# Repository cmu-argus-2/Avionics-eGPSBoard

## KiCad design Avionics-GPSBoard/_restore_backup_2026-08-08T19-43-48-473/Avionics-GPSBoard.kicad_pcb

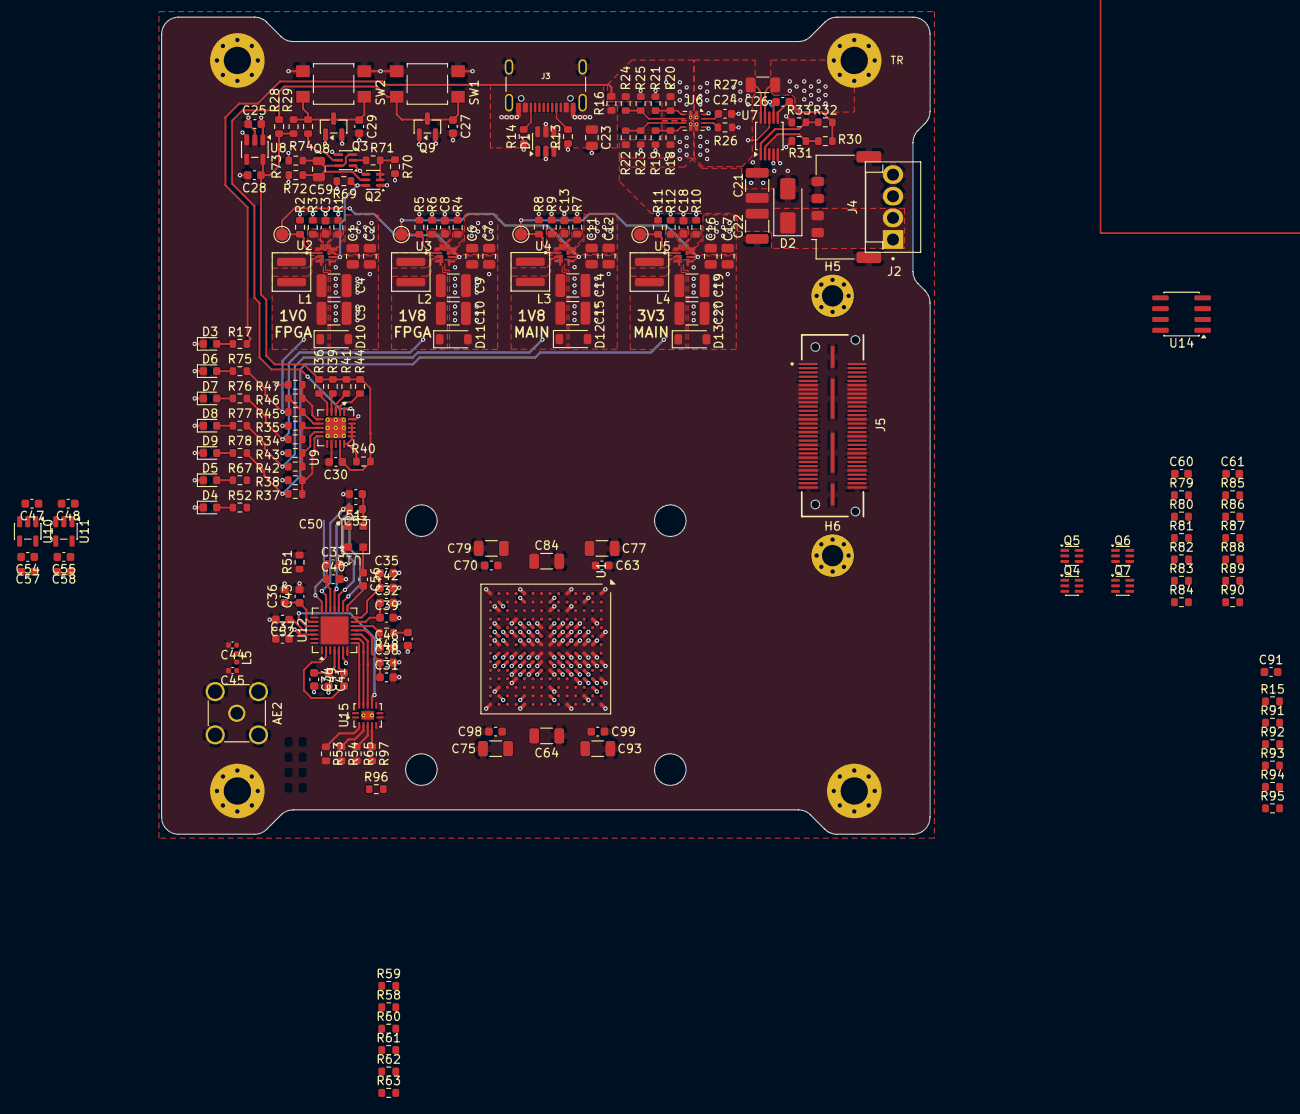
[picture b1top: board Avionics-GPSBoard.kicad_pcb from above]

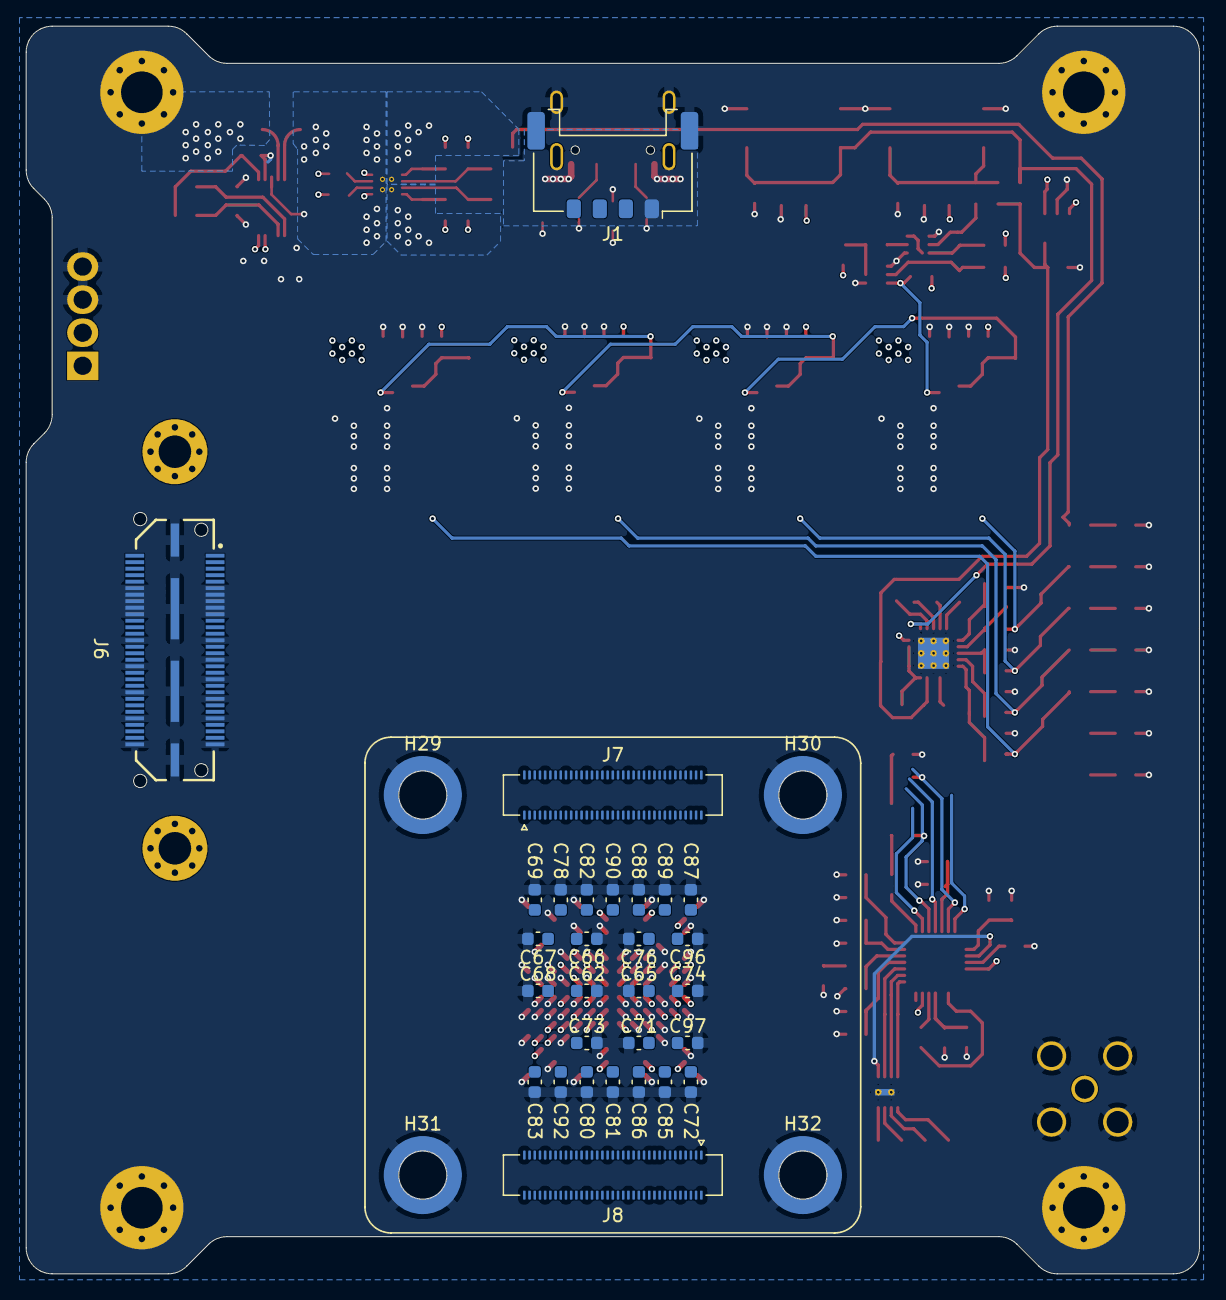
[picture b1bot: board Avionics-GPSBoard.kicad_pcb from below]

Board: 4 copper layers, 90.2 x 95.9 mm, 252 parts (33 on the bottom side), 119 nets.

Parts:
AE2: Antenna_Shield; SMA_Amphenol_132134-11_Vertical
C1, C2, C6, C7, C11, C12, C16, C17, C59: 10u; C_0805_2012Metric
C3, C8, C13, C18: 3n3; C_0603_1608Metric
C4, C5, C9, C10, C14, C15, C19, C20, C21, C22: 22u; C_1210_3225Metric
C23: 4u7; C_0805_2012Metric
C24: TBD; C_0603_1608Metric
C25, C47, C48, C54, C55: 1u; C_0603_1608Metric
C26, C27, C29, C30, C31, C32, C33, C34, C35, C36, C51, C57, C58: 100n; C_0603_1608Metric
C28: 2.2u; C_0603_1608Metric
C37, C49, C50: 470p; C_0603_1608Metric
C38, C39, C40, C41, C42, C43, C52: 100p; C_0603_1608Metric
C44, C45: TBD; C_0402_1005Metric
C46: 27p; C_0603_1608Metric
C53, C56, C60, C61: 10n; C_0603_1608Metric
C62, C65, C66, C67, C68, C71, C73, C74, C76, C80, C81, C82, C85, C86, C88, C89, C90, C96, C97: 470n; C_0603_1608Metric
C63, C69, C70, C72, C78, C83, C87, C91, C92, C98, C99: 4.7u; C_0603_1608Metric
C64, C79: 100u; C_1206_3216Metric
C75, C77, C84, C93: 47u; C_1206_3216Metric
D1: USBLC6-2SC6; SOT-23-6
D2: SMAJ9.0AHR3G; D_SMA
D3: Green; LED_0603_1608Metric
D4, D5: LED_G_0603_LTST-C190KRKT; LED_0603_1608Metric
D6, D7, D8, D9: LED_G_0603_LTST-C190GKT; LED_0603_1608Metric
D10, D11, D12, D13: SZMMSZ4685T1G; D_SOD-123
H1, H2, H3, H4: MountingHole_Pad; MountingHole_3.2mm_M3_Pad_Via
H5, H6: MountingHole_Pad; MountingHole_2.5mm_Pad_Via
H29, H30, H31, H32: 9774030151R; Mounting_Wuerth_WA-SMSI-M2.5_H3mm_9774030151
J1, J2: 205338-0004; Molex_Pico-Lock_205338-0004_1x04-1MP_P2.00mm_Horizontal
J3: USB4105-GF-A; USB_C_Receptacle_GCT_USB4105-xx-A_16P_TopMnt_Horizontal
J4: 282834-4; TE_282834-4
J5: QSH-030-01-L-D-A; SAMTEC_QSH-030-01-L-D-A
J6: QTH-030-01-L-D-A; SAMTEC-QTH-030-01-X-D-A
J7, J8: DF40HC(3.0)-70DS-0.4V; Hirose_DF40C-70DS-0.4V_2x35_P0.4mm
L1, L2, L3, L4: 2.2uH; L_Coilcraft_XAL4020-XXX
L5: 0R; L_0402_1005Metric
Q2, Q3, Q5, Q7: MBT2222ADW1T1; SOT-363_SC-70-6
Q4, Q6: NX3008NBKS; SOT-363_SC-70-6
Q8, Q9: BSS138; SOT-23
R1, R4, R7, R10: 61.9k; R_0603_1608Metric
R2, R5, R8, R11: 22k; R_0603_1608Metric
R3: 8.87k; R_0603_1608Metric
R6, R9: 21k; R_0603_1608Metric
R12: OPEN; R_0603_1608Metric
R13, R14: 5k1; R_0603_1608Metric
R15, R91, R92, R93, R94, R95: 1K; R_0603_1608Metric
R16, R30, R31, R32, R33, R51, R53, R54, R65, R81, R87, R97: 0R; R_0603_1608Metric
R17: 4k7; R_0603_1608Metric
R18, R19, R20, R21, R22, R23, R24, R25, R26, R34, R35, R37, R38, R40, R42, R43, R45, R46, R47: TBD; R_0603_1608Metric
R27: 10m; R_1206_3216Metric
R28, R29, R74, R82, R83, R88, R89, R96: 10k; R_0603_1608Metric
R36, R39, R41, R44, R70, R73, R80, R86: 100k; R_0603_1608Metric
R48, R71: 20k; R_0603_1608Metric
R52, R67, R75, R76, R77, R78: 2k7; R_0603_1608Metric
R58, R59, R60, R61, R62, R63: 33; R_0603_1608Metric
R69: 73k2; R_0603_1608Metric
R72, R84, R90: 200k; R_0603_1608Metric
R79, R85: 680R; R_0603_1608Metric
SW1, SW2: SW_Push; SW_SPST_TL3305A
TP1, TP2, TP3, TP4: TestPoint; TestPoint_Pad_D1.5mm
U1: XC7S50-L1FTGB196I; Xilinx_FTGB196
U2, U3, U4, U5: TPS62902QRYTRQ1
U6: TPS2121RUXR; Texas_VQFN-HR-12_2x2.5mm_P0.5mm_ThermalVias
U7: INA226-Q1; TSSOP-10_3x3mm_P0.5mm
U8: TPS70933DBVR-Q1; SOT-23-5
U9: TPS386000RGPR-Q1; Texas_RGP0020H_VQFN-20-1EP_4x4mm_P0.5mm_EP2.4x2.4mm_Thermal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
U10, U11: TPS7A20285PDBVR; SOT-23-5
U12: MAX2769BETI_V_T; TQFN-28-1EP_5x5mm_P0.5mm_EP3.25x3.25mm
U13: D32G-016_368M
U14: APS1604M-3SQRx-SN; SOIC-8_3.9x4.9mm_P1.27mm
U15: NXU0104BQ; DHVQFN-14-1EP_2.5x3mm_P0.5mm_EP1x1.5mm_ThermalVias

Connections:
2V85_RF_A: C31.1, C32.1, C34.1, C35.1, C36.1, C38.1, C39.1, C41.1, C42.1, C43.1, C54.1, C57.1, R52.1, U10.5 (OUT), U12.4 (VCCRF), U12.11 (VCCVCO), U12.13 (VCCCP), U12.14 (VCCD), U12.23 (VCCIF)
2V85_RF_D: C33.1, C40.1, C51.1, C53.1, C55.1, C58.1, R67.1, R96.1, U11.5 (OUT), U12.19 (VCCADC), U13.4 (VCC), U15.8 (OE), U15.14 (VCCB)
+1V0_F: C4.2, C5.2, C62.1, C63.1, C64.1, C65.1, C66.1, C67.1, C68.1, C69.1, C70.1, C76.1, C77.1, C78.1, C79.1, D10.1 (K), L1.2, R45.2, R75.2, U1.D6 (VCCINT), U1.D8 (VCCINT), U1.E5 (VCCBRAM), U1.E7 (VCCINT), U1.E9 (VCCINT), U1.F6 (VCCINT), U1.G5 (VCCBRAM), U1.G9 (VCCINT), U1.H6 (VCCINT), U1.J5 (VCCBRAM), U1.J9 (VCCINT), U1.K6 (VCCINT), U1.K8 (VCCINT), U2.3 (VOS)
+1V8_DCDC: J8.3, J8.5, J8.7
+1V8_F: C9.2, C10.2, C71.1, C72.1, C73.1, C74.1, C75.1, C80.1, C81.1, C82.1, C83.1, C84.1, C85.1, C86.1, C87.1, C88.1, C89.1, C90.1, C91.1, C92.1, C93.1, C96.1, C97.1, C98.1, C99.1, D11.1 (K), L2.2, R15.1, R34.2, R76.2, R92.1, R94.1, U1.F8 (VCCADC_0), U1.F10 (VCCAUX), U1.G2 (VCCO_34), U1.G13 (VCCO_14), U1.H10 (VCCAUX), U1.K2 (VCCO_34), U1.K10 (VCCAUX), U1.K13 (VCCO_14), U1.L9 (VCCAUX), U1.N2 (VCCO_34), U1.N6 (VCCO_0), U1.N8 (VCCO_0), U1.N13 (VCCO_14), U3.3 (VOS), U14.8 (VDD)
+1V8_M: C14.2, C15.2, D12.1 (K), L3.2, R42.2, R77.2, U4.3 (VOS), U15.1 (VCCA)
+3V3_M: C19.2, C20.2, C26.2, C47.1, C48.1, D13.1 (K), L4.2, R30.2, R32.2, R37.2, R78.2, R80.1, R82.1, R83.1, R86.1, R88.1, R89.1, U5.3 (VOS), U7.6 (VS), U10.1 (IN), U11.1 (IN)
+3V3_SUP: C28.1, C30.2, R28.1, R29.1, R36.1, R39.1, R40.1, R41.1, R44.1, U8.5 (OUT), U9.14 (VCC)
/FPGA/MODE0: R15.2, R91.1, U1.M7 (M0_0)
/FPGA/MODE1: R92.2, R93.1, U1.M8 (M1_0)
/FPGA/MODE2: R94.2, R95.1, U1.M9 (M2_0)
/FPGA/QSPI_CS: U1.C11 (IO_L6P_T0_FCS_B_14), U14.1 (~CE)
/FPGA/QSPI_DO0: U1.B11 (IO_L1P_T0_D00_MOSI_14), U14.5 (SI/SIO0)
/FPGA/QSPI_DO1: U1.B12 (IO_L1N_T0_D01_DIN_14), U14.2 (SO/SIO1)
/FPGA/QSPI_DO2: U1.D10 (IO_L2P_T0_D02_14), U14.3 (SIO2)
/FPGA/QSPI_DO3: U1.C10 (IO_L2N_T0_D03_14), U14.7 (SIO3)
/FPGA/QSPI_SCK: U1.A8 (CCLK_0), U14.6 (SCLK)
/Main Power/+1V0_F_EN: Q2.6 (C1), R69.2, U2.5 (EN)
/Main Power/DCDC1/PG: R5.2, TP2.1 (1_1), U3.1 (PG), U4.5 (EN)
/Main Power/DCDC2/PG: R8.2, TP3.1 (1_1), U4.1 (PG), U5.5 (EN)
/Main Power/DCDC3/PG: R11.2, TP4.1 (1_1), U5.1 (PG)
/Main Power/DCDC/PG: R2.2, TP1.1 (1_1), U2.1 (PG), U3.5 (EN)
/Main Power/HARD_RESET: C29.2, Q8.3 (D), R29.2, R74.2, SW2.2
/Power Monitoring/A0_M: R30.1, R31.2, U7.2 (A0)
/Power Monitoring/A1_M: R32.1, R33.2, U7.1 (A1)
/Power Monitoring/CT1: R36.2, U9.5 (CT1)
/Power Monitoring/CT2: R39.2, U9.4 (CT2)
/Power Monitoring/CT3: R41.2, U9.3 (CT3)
/Power Monitoring/CT4: R44.2, U9.2 (CT4)
/Power Monitoring/I2C Protection/SCL_DEVICE: Q5.4 (E2), Q5.6 (C1), R81.1, R83.2, R84.1, U7.5 (SCL)
/Power Monitoring/I2C Protection/SDA_DEVICE: Q7.4 (E2), Q7.6 (C1), R87.1, R89.2, R90.1, U7.4 (SDA)
/Power Monitoring/MR: C27.2, Q9.3 (D), R28.2, SW1.2, U9.1 (~MR)
/Power Monitoring/SCL: Q5.1 (E1), Q5.3 (C2), R81.2
/Power Monitoring/SDA: Q7.1 (E1), Q7.3 (C2), R87.2
/Power Monitoring/SNS1: R37.1, R38.1, U9.10 (SENSE1)
/Power Monitoring/SNS2: R42.1, R43.1, U9.9 (SENSE2)
/Power Monitoring/SNS3: R34.1, R35.1, U9.8 (SENSE3)
/Power Monitoring/SNS4H: R46.2, R47.1, U9.6 (SENSE4H)
/Power Monitoring/SNS4L: R45.1, R46.1, U9.7 (SENSE4L)
/Power Monitoring/SOFT_RESET: R40.2, U9.15 (~RESET1), U9.16 (~RESET2), U9.17 (~RESET3), U9.18 (~RESET4), U9.19 (~WDO)
/Power Selection/CP2: R20.1, R21.1, U6.3 (CP2)
/Power Selection/D_UP+: D1.6 (I/O1), J1.2, J3.A6 (D+), J3.B6 (D+)
/Power Selection/D_UP-: D1.4 (I/O2), J1.3, J3.A7 (D-), J3.B7 (D-)
/Power Selection/OV1: R22.1, R23.1, U6.5 (OV1)
/Power Selection/OV2: R24.1, R25.1, U6.4 (OV2)
/Power Selection/PR1: R18.1, R19.1, U6.6 (PR1)
/Power Selection/VUSB_IN: C23.1, D1.5 (VBUS), J1.1, J3.A4 (VBUS), J3.A9 (VBUS), J3.B4 (VBUS), J3.B9 (VBUS), R16.1
/RF Receiver/CLKOUT: R59.1, R59.2, U12.16 (CLKOUT)
/RF Receiver/I0: R60.1, R60.2, U12.20 (I0)
/RF Receiver/I1: R61.1, R61.2, U12.21 (I1)
/RF Receiver/LD: R58.1, U12.6 (LD)
/RF Receiver/Q0: R62.1, R62.2, U12.18 (Q0)
/RF Receiver/Q1: R63.1, R63.2, U12.17 (Q1)
/RF Receiver/REG_nSHDN_I: U10.3 (EN), U11.3 (EN)
/RF Receiver/RF_CPOUT: C46.1, R48.2, U12.12 (CPOUT)
/RF Receiver/RF_LNA1: C37.2, U12.27 (LNA1)
/RF Receiver/RF_LNA2: C52.1, U12.25 (LNA2)
/RF Receiver/RF_LNAOUT: C49.1, U12.2 (LNAOUT)
/RF Receiver/RF_MIXIN: C49.2, U12.5 (MIXIN)
/RF Receiver/RF_PG: R51.1, U12.26 (PGM)
/RF Receiver/RF_XTAL: C56.2, U12.15 (XTAL)
/RF Receiver/SCLK: U12.9 (SCLK), U15.12 (YB2)
/RF Receiver/SDATA: U12.8 (SDATA), U15.13 (YB1)
/RF Receiver/nCS: U12.10 (~CS), U15.11 (YB3)
/RF Receiver/nIDLE_I: U12.24 (~IDLE), U15.10 (YB4)
/RF Receiver/nSHDN: R96.2, U12.7 (~SHDN)
GND: AE2.2 (Shield), C1.2, C2.2, C3.1, C4.1, C5.1, C6.2, C7.2, C8.1, C9.1, C10.1, C11.2, C12.2, C13.1, C14.1, C15.1, C16.2, C17.2, C18.1, C19.1, C20.1, C21.2, C22.2, C23.2, C24.1, C25.2, C26.1, C27.1, C28.2, C29.1, C30.1, C31.2, C32.2, C33.2, C34.2, C35.2, C36.2, C38.2, C39.2, C40.2, C41.2, C42.2, C43.2, C44.2, C45.2, C46.2, C47.2, C48.2, C50.2, C51.2, C52.2, C53.2, C54.2, C55.2, C57.2, C58.2, C60.2, C61.2, C62.2, C63.2, C64.2, C65.2, C66.2, C67.2, C68.2, C69.2, C70.2, C71.2, C72.2, C73.2, C74.2, C75.2, C76.2, C77.2, C78.2, C79.2, C80.2, C81.2, C82.2, C83.2, C84.2, C85.2, C86.2, C87.2, C88.2, C89.2, C90.2, C91.2, C92.2, C93.2, C96.2, C97.2, C98.2, C99.2, D1.2 (GND), D2.2 (A), D3.1 (K), D4.1 (K), D5.1 (K), D6.1 (K), D7.1 (K), D8.1 (K), D9.1 (K), D10.2 (A), D11.2 (A), D12.2 (A), D13.2 (A), H1.1 (1_1), H2.1 (1_1), H3.1 (1_1), H4.1 (1_1), H29.1 (1_1), H30.1 (1_1), H31.1 (1_1), H32.1 (1_1), J1.4, J1.MP (MountPin), J2.3, J2.4, J2.MP (MountPin), J3.A1 (GND), J3.A12 (GND), J3.B1 (GND), J3.B12 (GND), J3.SH (SHIELD), J4.3, J4.4, J5.11, J5.12, J5.13, J5.14, J5.15, J5.16, J5.17, J5.18, J5.19, J5.20, J5.27, J5.28, J5.33, J5.36, J5.39, J5.44, J5.45, J5.51, J5.52, J5.59, J5.60, J5.SH (Shield), J6.11, J6.12, J6.13, J6.14, J6.15, J6.16, J6.17, J6.18, J6.19, J6.20, J6.27, J6.28, J6.33, J6.36, J6.39, J6.44, J6.45, J6.51, J6.52, J6.59, J6.60, J6.SH (Shield), J7.1, J7.2, J7.9, J7.10, J7.17, J7.18, J7.25, J7.26, J7.33, J7.34, J7.41, J7.42, J7.49, J7.50, J7.57, J7.58, J7.65, J7.66, J7.67, J7.68, J7.69, J7.70, J8.1, J8.2, J8.9, J8.10, J8.17, J8.18, J8.19, J8.21, J8.22, J8.29, J8.30, J8.37, J8.38, J8.45, J8.46, J8.53, J8.54, J8.61, J8.62, J8.69, J8.70, Q2.1 (E1), Q2.4 (E2), Q3.1 (E1), Q3.4 (E2), Q4.1 (S2), Q4.4 (S1), Q6.1 (S2), Q6.4 (S1), Q8.2 (S), Q9.2 (S), R1.1, R3.1, R4.1, R6.1, R7.1, R9.1, R10.1, R12.1, R13.1, R14.1, R19.2, R21.2, R23.2, R25.2, R26.2, R31.1, R33.1, R35.2, R38.2, R43.2, R47.2, R51.2, R91.2, R93.2, R95.2, SW1.1, SW2.1, U1.A1 (GND), U1.A6 (GND), U1.A9 (GND), U1.A11 (GND), U1.A14 (GND), U1.B4 (GND), U1.B7 (GND), U1.B8 (VCCBATT_0), U1.B9 (GND), U1.C2 (GND), U1.C6 (GND), U1.C7 (GND), U1.C8 (GND), U1.C9 (GND), U1.C13 (GND), U1.D5 (GND), U1.D7 (GND), U1.D9 (GND), U1.D11 (GND), U1.E1 (GND), U1.E3 (GND), U1.E6 (GND), U1.E8 (GND), U1.E10 (GND), U1.E14 (GND), U1.F5 (GND), U1.F7 (GNDADC_0), U1.F9 (GND), U1.G3 (GND), U1.G6 (GND), U1.G7 (VREFN_0), U1.G8 (VP_0), U1.G10 (GND), U1.G12 (GND), U1.H5 (GND), U1.H7 (VN_0), U1.H8 (VREFP_0), U1.H9 (GND), U1.J6 (GND), U1.J7 (DXN_0), U1.J8 (DXP_0), U1.J10 (GND), U1.K1 (GND), U1.K5 (GND), U1.K7 (GND), U1.K9 (GND), U1.K14 (GND), U1.L4 (GND), U1.L6 (GND), U1.L8 (GND), U1.L10 (GND), U1.L11 (GND), U1.N3 (GND), U1.N5 (GND), U1.N7 (CFGBVS_0), U1.N9 (GND), U1.N12 (GND), U1.P1 (GND), U1.P14 (GND), U2.4 (GND), U3.4 (GND), U4.4 (GND), U5.4 (GND), U6.9 (ST), U6.12 (GND), U7.7 (GND), U8.2 (GND), U9.12 (GND), U9.21 (EP), U10.2 (GND), U10.4 (NC), U11.2 (GND), U11.4 (NC), U12.29 (EP), U13.2 (GND), U14.4 (VSS), U15.7 (GND), U15.15 (EP)
unnamed: AE2.1 (A), C45.1, L5.2
unnamed: C37.1, C44.1, L5.1
unnamed: C50.1, R48.1
unnamed: D3.2 (A), R17.2
unnamed: D4.2 (A), R52.2
unnamed: D5.2 (A), R67.2
unnamed: D6.2 (A), R75.1
unnamed: D7.2 (A), R76.1
unnamed: D8.2 (A), R77.1
unnamed: D9.2 (A), R78.1
unnamed: J3.A5 (CC1), R13.2
unnamed: J3.B5 (CC2), R14.2
unnamed: Q2.2 (B1), Q2.3 (C2), R70.2, R71.2
unnamed: C59.2, Q2.5 (B2), R72.2
unnamed: Q3.2 (B1), R71.1
unnamed: C59.1, Q3.3 (C2), Q3.6 (C1), R73.2
unnamed: Q3.5 (B2), R74.1
unnamed: Q4.6 (D1), Q5.5 (B2), R79.2, R82.2
unnamed: Q4.2 (G2), Q4.3 (D2), R80.2
unnamed: C60.1, Q4.5 (G1), R84.2
unnamed: Q5.2 (B1), R79.1
unnamed: Q6.6 (D1), Q7.5 (B2), R85.2, R88.2
unnamed: Q6.2 (G2), Q6.3 (D2), R86.2
unnamed: C61.1, Q6.5 (G1), R90.2
unnamed: Q7.2 (B1), R85.1
unnamed: R3.2, U2.9 (FB/VSET)
unnamed: R1.2, U2.7 (MODE/S-CONF)
unnamed: C3.2, U2.8 (SS/TR)
unnamed: L1.1, U2.2 (SW)
unnamed: R6.2, U3.9 (FB/VSET)
unnamed: R4.2, U3.7 (MODE/S-CONF)
unnamed: C8.2, U3.8 (SS/TR)
unnamed: L2.1, U3.2 (SW)
unnamed: R9.2, U4.9 (FB/VSET)
unnamed: R7.2, U4.7 (MODE/S-CONF)
unnamed: C13.2, U4.8 (SS/TR)
unnamed: L3.1, U4.2 (SW)
unnamed: R12.2, U5.9 (FB/VSET)
unnamed: R10.2, U5.7 (MODE/S-CONF)
unnamed: C18.2, U5.8 (SS/TR)
unnamed: L4.1, U5.2 (SW)
unnamed: R26.1, U6.10 (ILIM)
unnamed: C24.2, U6.11 (SS)
unnamed: C56.1, U13.3 (OUT)
unnamed: R53.1, U15.2 (A1)
unnamed: R54.1, U15.3 (A2)
unnamed: R65.1, U15.4 (A3)
unnamed: R97.1, U15.5 (A4)
VBATT: C21.1, C22.1, D2.1 (K), J2.1, J2.2, J4.1, J4.2, J5.1, J5.2, J5.3, J5.4, J5.5, J5.6, J5.7, J5.8, J5.9, J5.10, J6.1, J6.2, J6.3, J6.4, J6.5, J6.6, J6.7, J6.8, J6.9, J6.10, R18.2, R22.2, U6.7 (IN1)
VSYS: C1.1, C2.1, C6.1, C7.1, C11.1, C12.1, C16.1, C17.1, C25.1, R2.1, R5.1, R8.1, R11.1, R27.1, R69.1, R70.1, R72.1, R73.1, U2.6 (VIN), U3.6 (VIN), U4.6 (VIN), U5.6 (VIN), U7.9 (Vin-), U8.1 (IN), U8.3 (EN)
VSYS_S: R27.2, U6.1 (OUT), U6.8 (OUT), U7.8 (Vbus), U7.10 (Vin+)
VUSB: R16.2, R17.1, R20.2, R24.2, U6.2 (IN2)

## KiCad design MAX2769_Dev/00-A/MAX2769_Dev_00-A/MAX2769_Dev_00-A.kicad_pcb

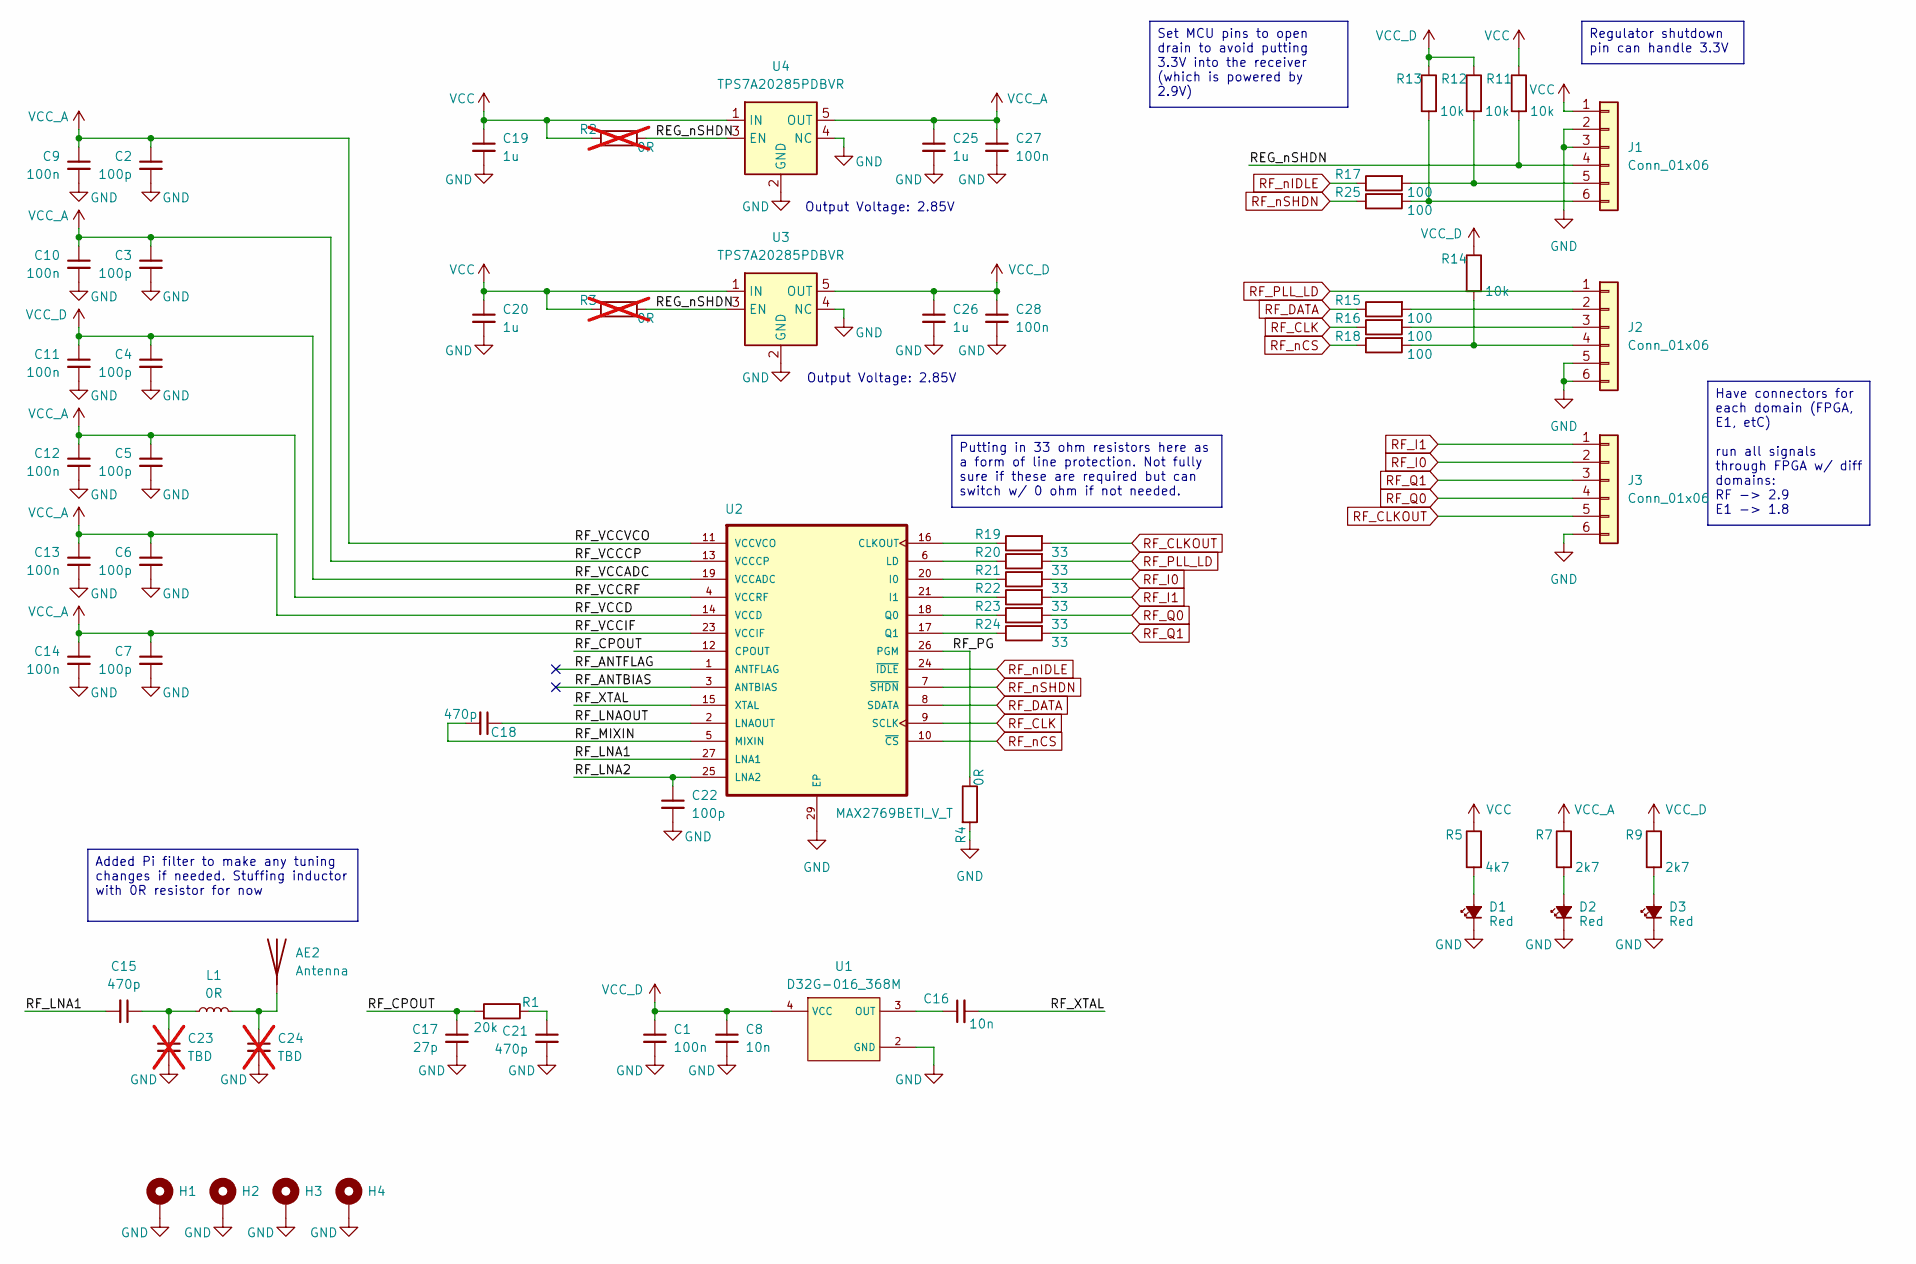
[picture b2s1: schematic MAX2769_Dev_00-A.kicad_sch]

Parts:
AE2: Antenna; CGGBP_18_4_A_02
C1, C9, C10, C11, C12, C13, C14, C27, C28: 100n; C_0603_1608Metric
C2, C3, C4, C5, C6, C7, C22: 100p; C_0603_1608Metric
C8, C16: 10n; C_0603_1608Metric
C15, C18, C21: 470p; C_0603_1608Metric
C17: 27p; C_0603_1608Metric
C19, C20, C25, C26: 1u; C_0603_1608Metric
C23, C24: TBD; C_0402_1005Metric; not fitted
D1, D2, D3: LED_G_0603_LTST-C190KRKT; LED_0603_1608Metric; MPN C2909774
H1, H2, H3, H4: MountingHole_Pad_MP; MountingHole_2.7mm_M2.5_Pad_Via
J1, J2, J3: Conn_01x06; PinHeader_1x06_P2.54mm_Vertical
L1: 0R; L_0402_1005Metric
R1: 20k; R_0603_1608Metric
R2, R3: 0R; R_0603_1608Metric; not fitted
R4: 0R; R_0603_1608Metric
R5: 4k7; R_0603_1608Metric
R7, R9: 2k7; R_0603_1608Metric
R11, R12, R13, R14: 10k; R_0603_1608Metric
R15, R16, R17, R18, R25: 100; R_0603_1608Metric
R19, R20, R21, R22, R23, R24: 33; R_0603_1608Metric
U1: D32G-016_368M
U2: MAX2769BETI_V_T; QFN50P500X500X80-29N
U3, U4: TPS7A20285PDBVR; SOT-23-5

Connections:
/REG_nSHDN: J1.4, R2.1, R3.1, R11.2, U3.3 (EN), U4.3 (EN)
/RF_ANTBIAS: U2.3 (ANTBIAS)
/RF_ANTFLAG: U2.1 (ANTFLAG)
/RF_CPOUT: C17.1, R1.2, U2.12 (CPOUT)
/RF_LNA1: C15.2, U2.27 (LNA1)
/RF_LNA2: C22.1, U2.25 (LNA2)
/RF_LNAOUT: C18.1, U2.2 (LNAOUT)
/RF_MIXIN: C18.2, U2.5 (MIXIN)
/RF_PG: R4.1, U2.26 (PGM)
/RF_XTAL: C16.2, U2.15 (XTAL)
GND: C1.2, C2.2, C3.2, C4.2, C5.2, C6.2, C7.2, C8.2, C9.2, C10.2, C11.2, C12.2, C13.2, C14.2, C17.2, C19.2, C20.2, C21.2, C22.2, C23.2, C24.2, C25.2, C26.2, C27.2, C28.2, D1.1 (K), D2.1 (K), D3.1 (K), H1.1 (1_1), H2.1 (1_1), H3.1 (1_1), H4.1 (1_1), J1.2, J1.3, J2.5, J2.6, J3.6, R4.2, U1.2 (GND), U2.29 (EP), U3.2 (GND), U3.4 (NC), U4.2 (GND), U4.4 (NC)
unnamed: AE2.1 (A_1), C24.1, L1.2
unnamed: C15.1, C23.1, L1.1
unnamed: C21.1, R1.1
unnamed: D1.2 (A), R5.2
unnamed: D2.2 (A), R7.2
unnamed: D3.2 (A), R9.2
unnamed: J1.5, R12.2, R17.2
unnamed: J1.6, R13.2, R25.2
unnamed: J2.2, R15.2
unnamed: J2.3, R16.2
unnamed: J2.4, R14.2, R18.2
unnamed: C16.1, U1.3 (OUT)
unnamed: R19.1, U2.16 (CLKOUT)
unnamed: R21.1, U2.20 (I0)
unnamed: R22.1, U2.21 (I1)
unnamed: R20.1, U2.6 (LD)
unnamed: R23.1, U2.18 (Q0)
unnamed: R24.1, U2.17 (Q1)
RF_CLK: R16.1, U2.9 (SCLK)
RF_CLKOUT: J3.5, R19.2
RF_DATA: R15.1, U2.8 (SDATA)
RF_I0: J3.2, R21.2
RF_I1: J3.1, R22.2
RF_PLL_LD: J2.1, R20.2
RF_Q0: J3.4, R23.2
RF_Q1: J3.3, R24.2
RF_nCS: R18.1, U2.10 (~CS)
RF_nIDLE: R17.1, U2.24 (~IDLE)
RF_nSHDN: R25.1, U2.7 (~SHDN)
VCC: C19.1, C20.1, J1.1, R2.2, R3.2, R5.1, R11.1, U3.1 (IN), U4.1 (IN)
VCC_A: C2.1, C3.1, C5.1, C6.1, C7.1, C9.1, C10.1, C12.1, C13.1, C14.1, C25.1, C27.1, R7.1, U2.4 (VCCRF), U2.11 (VCCVCO), U2.13 (VCCCP), U2.14 (VCCD), U2.23 (VCCIF), U4.5 (OUT)
VCC_D: C1.1, C4.1, C8.1, C11.1, C26.1, C28.1, R9.1, R12.1, R13.1, R14.1, U1.4 (VCC), U2.19 (VCCADC), U3.5 (OUT)

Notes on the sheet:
Output Voltage: 2.85V
Added Pi filter to make any tuning changes if needed. Stuffing inductor with 0R resistor for now
Putting in 33 ohm resistors here as a form of line protection. Not fully sure if these are required but can switch w/ 0 ohm if not needed.
Have connectors for each domain (FPGA, E1, etC) run all signals through FPGA w/ diff domains: RF -> 2.9 E1 -> 1.8
Set MCU pins to open drain to avoid putting 3.3V into the receiver (which is powered by 2.9V)
Regulator shutdown pin can handle 3.3V

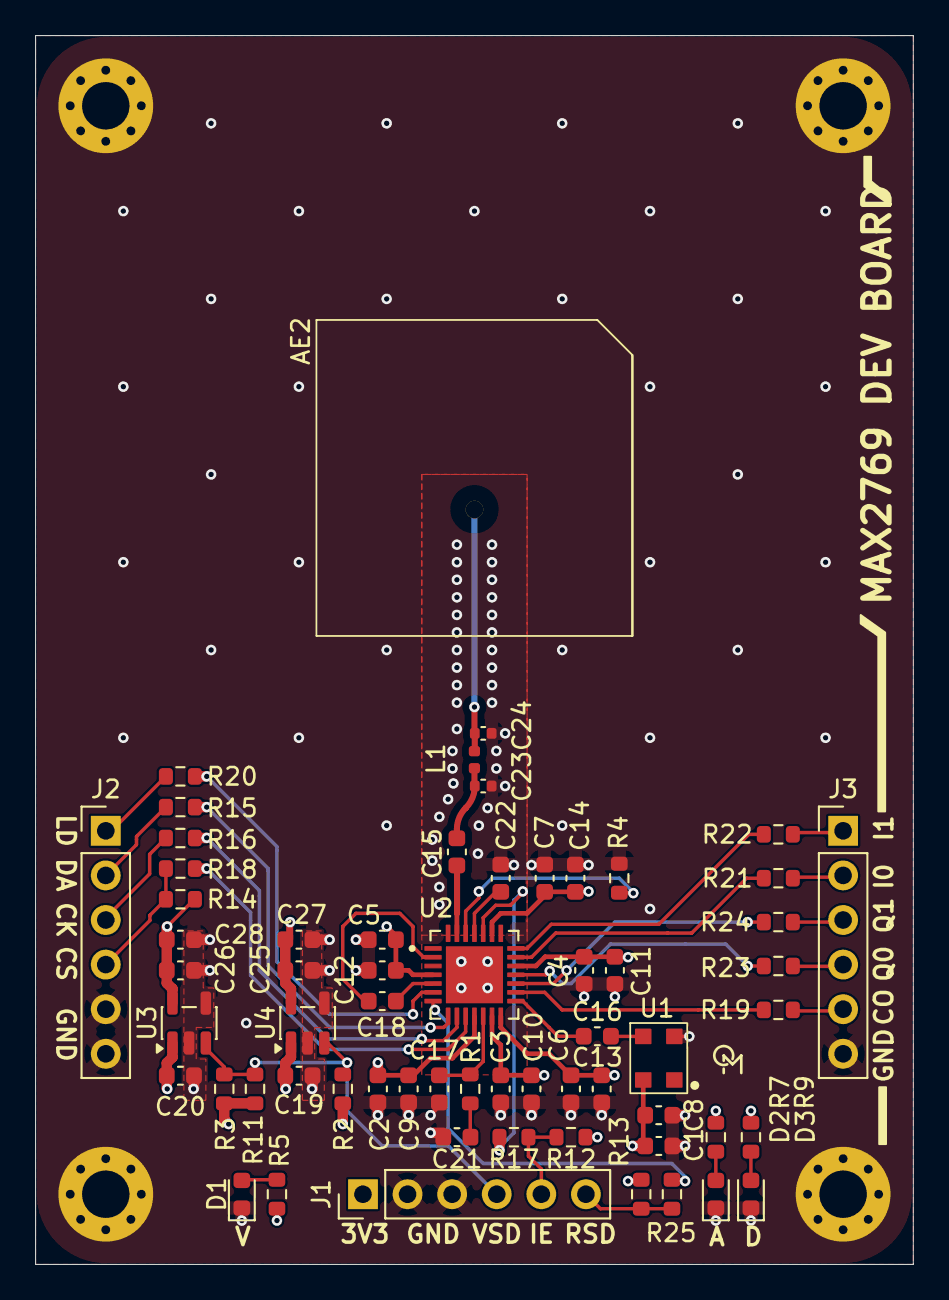
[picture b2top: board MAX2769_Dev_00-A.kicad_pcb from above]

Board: 4 copper layers, 50.0 x 70.0 mm, 66 parts (0 on the bottom side), 41 nets.
